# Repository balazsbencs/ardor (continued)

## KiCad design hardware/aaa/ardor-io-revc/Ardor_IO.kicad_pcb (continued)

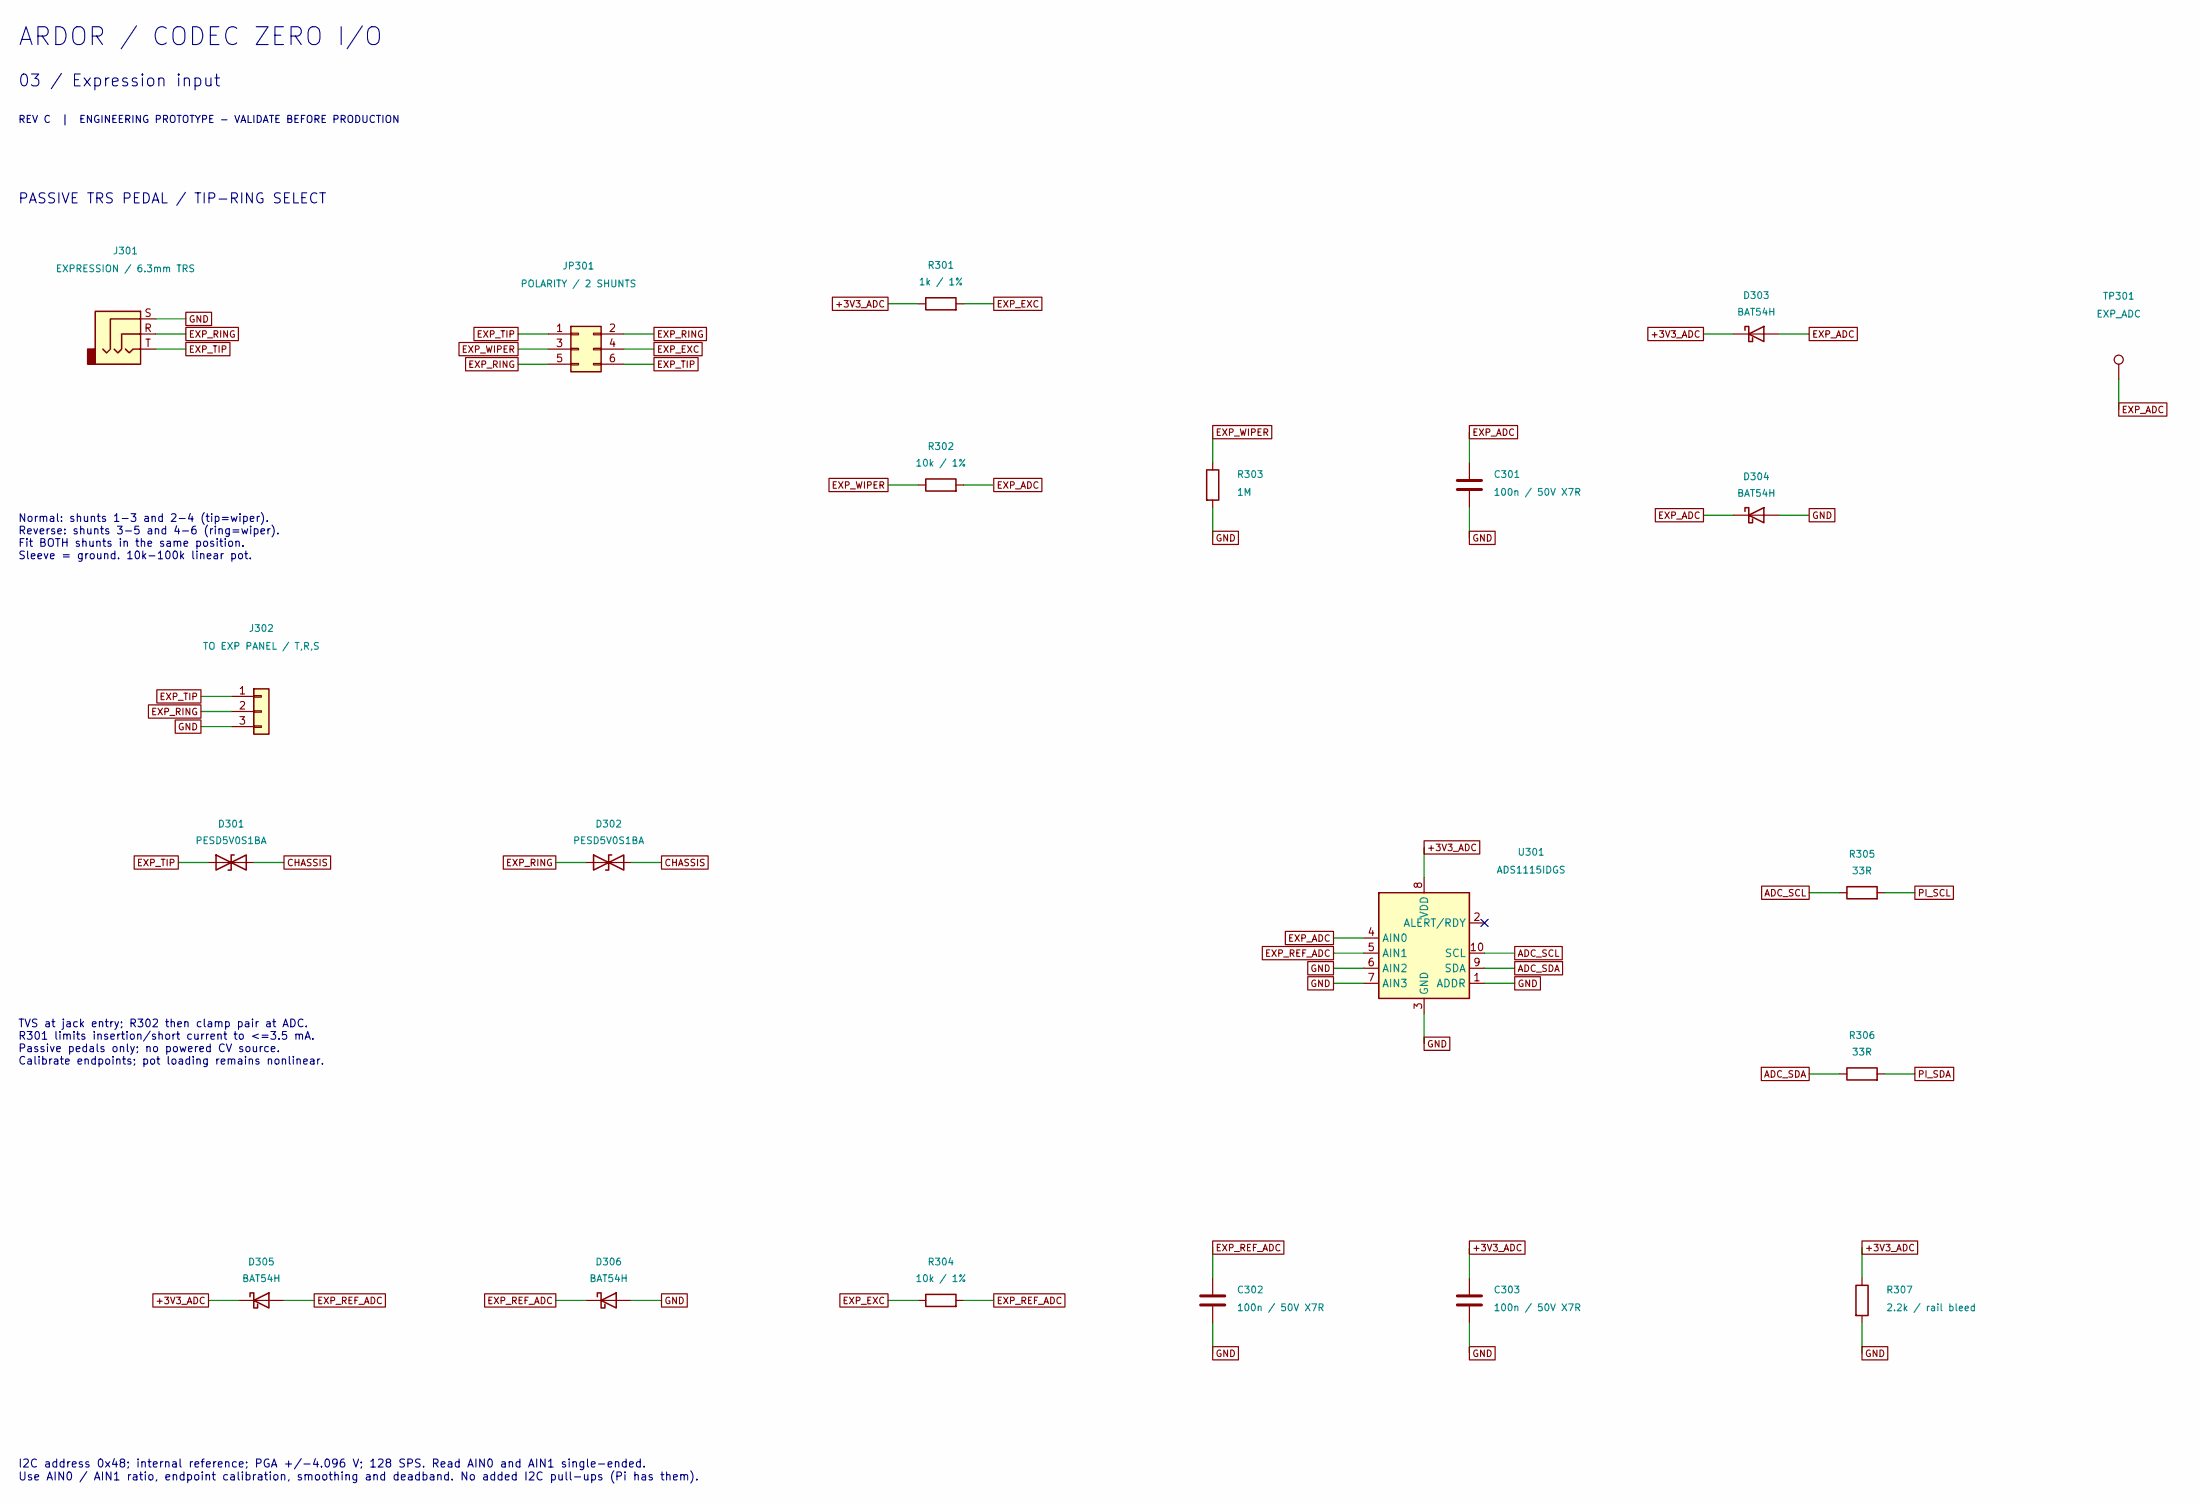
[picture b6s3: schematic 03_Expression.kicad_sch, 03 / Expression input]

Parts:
C301, C302, C303: 100n / 50V X7R; C_0603_1608Metric; MPN YAGEO CC0603KRX7R9BB104; JLCPCB Part # C14663
D301, D302: PESD5V0S1BA; D_SOD-323; MPN Nexperia PESD5V0S1BA,115; JLCPCB Part # C19224
D303, D304, D305, D306: BAT54H; D_SOD-123F; MPN Nexperia BAT54H,115; JLCPCB Part # C426769
J301: EXPRESSION / 6.3mm TRS
J302: TO EXP PANEL / T,R,S; PinHeader_1x03_P2.54mm_Vertical
JP301: POLARITY / 2 SHUNTS; PinHeader_2x03_P2.54mm_Vertical
R301: 1k / 1%; R_0603_1608Metric; MPN UNI-ROYAL 0603WAF1001T5E; JLCPCB Part # C21190
R302, R304: 10k / 1%; R_0603_1608Metric; MPN UNI-ROYAL 0603WAF1002T5E; JLCPCB Part # C25804
R303: 1M; R_0603_1608Metric; MPN UNI-ROYAL 0603WAF1004T5E; JLCPCB Part # C22935
R305, R306: 33R; R_0603_1608Metric; MPN UNI-ROYAL 0603WAF330JT5E; JLCPCB Part # C23140
R307: 2.2k / rail bleed; R_0603_1608Metric; MPN UNI-ROYAL 0603WAF2201T5E; JLCPCB Part # C4190
TP301: EXP_ADC; TestPoint_Pad_D1.5mm
U301: ADS1115IDGS; VSSOP-10_3x3mm_P0.5mm; MPN TI ADS1115IDGSR; JLCPCB Part # C37593

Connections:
+3V3_ADC: C303.1, D303.1 (K), D305.1 (K), R301.1, R307.1, U301.8 (VDD); also elsewhere on the board
ADC_SCL: R305.1, U301.10 (SCL)
ADC_SDA: R306.1, U301.9 (SDA)
CHASSIS: D301.2 (A2), D302.2 (A2); also elsewhere on the board
EXP_ADC: C301.1, D303.2 (A), D304.1 (K), R302.2, TP301.1, U301.4 (AIN0)
EXP_EXC: JP301.4, R301.2, R304.1
EXP_REF_ADC: C302.1, D305.2 (A), D306.1 (K), R304.2, U301.5 (AIN1)
EXP_RING: D302.1 (A1), J301.R, J302.2, JP301.2, JP301.5
EXP_TIP: D301.1 (A1), J301.T, J302.1, JP301.1, JP301.6
EXP_WIPER: JP301.3, R302.1, R303.1
GND: C301.2, C302.2, C303.2, D304.2 (A), D306.2 (A), J301.S, J302.3, R303.2, R307.2, U301.1 (ADDR), U301.3 (GND), U301.6 (AIN2), U301.7 (AIN3); also elsewhere on the board
PI_SCL: R305.2; also elsewhere on the board
PI_SDA: R306.2; also elsewhere on the board

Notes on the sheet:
ARDOR / CODEC ZERO I/O
03 / Expression input
REV C | ENGINEERING PROTOTYPE - VALIDATE BEFORE PRODUCTION
PASSIVE TRS PEDAL / TIP-RING SELECT
Normal: shunts 1-3 and 2-4 (tip=wiper). Reverse: shunts 3-5 and 4-6 (ring=wiper). Fit BOTH shunts in the same position. Sleeve = ground. 10k-100k linear pot.
TVS at jack entry; R302 then clamp pair at ADC. R301 limits insertion/short current to <=3.5 mA. Passive pedals only; no powered CV source. Calibrate endpoints; pot loading remains nonlinear.
I2C address 0x48; internal reference; PGA +/-4.096 V; 128 SPS. Read AIN0 and AIN1 single-ended. Use AIN0 / AIN1 ratio, endpoint calibration, smoothing and deadband. No added I2C pull-ups (Pi has them).

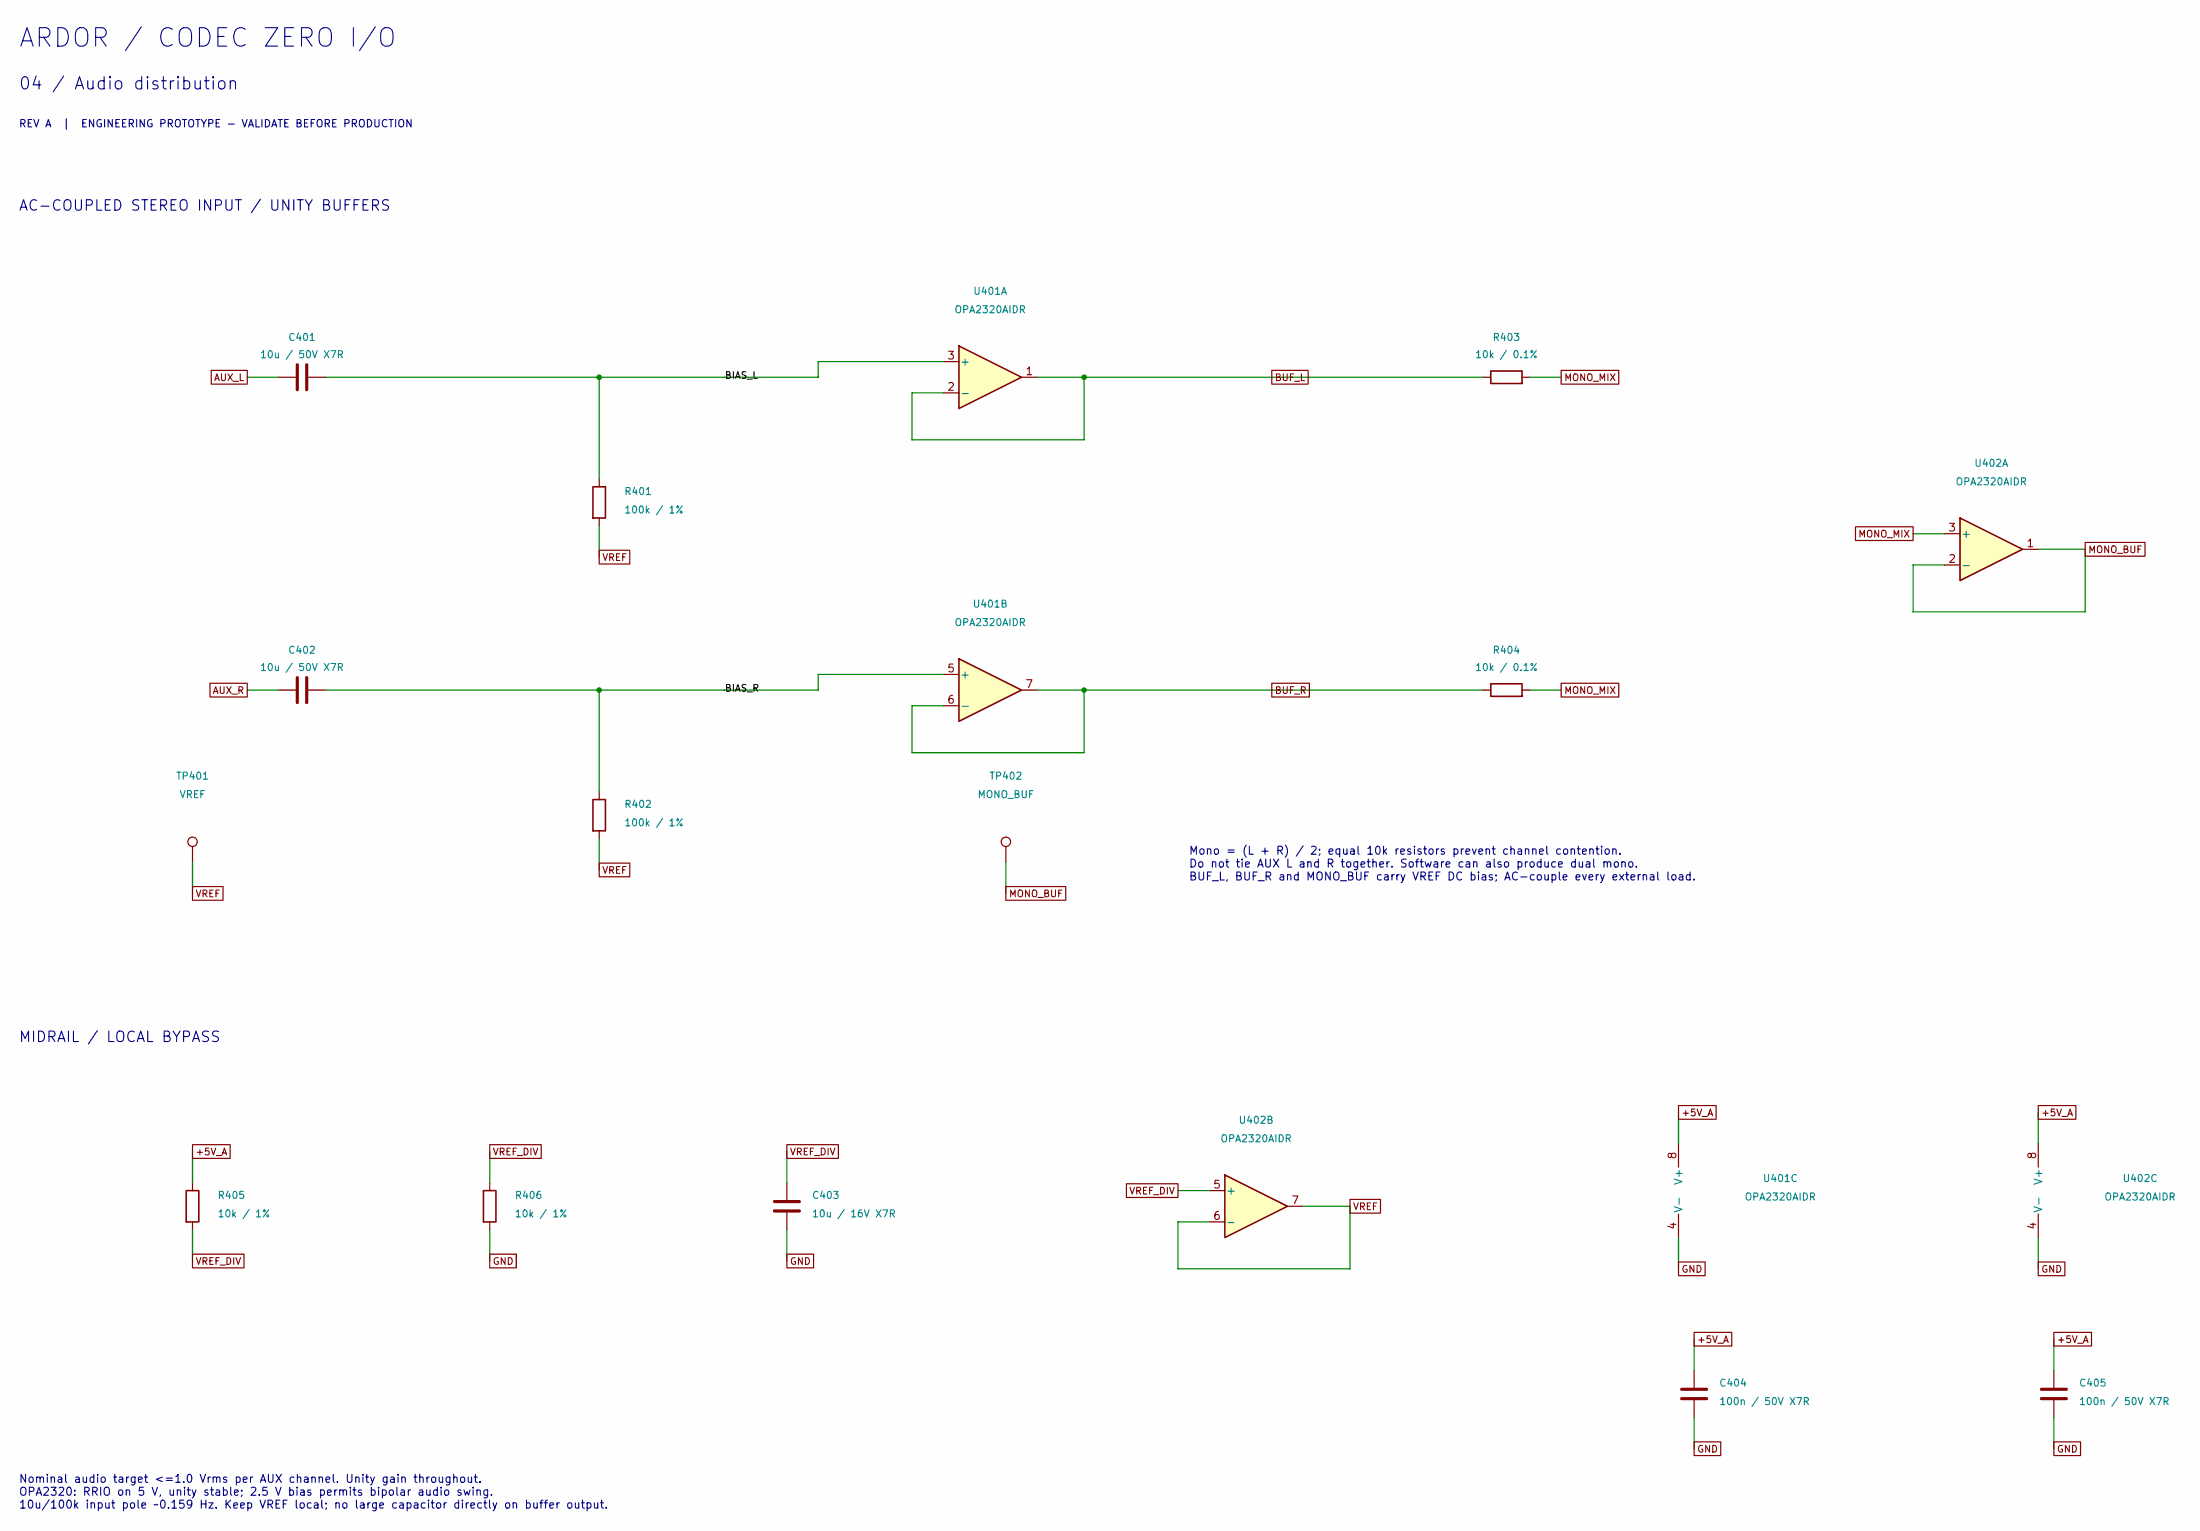
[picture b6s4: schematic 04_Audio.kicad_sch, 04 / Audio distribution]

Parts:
C401, C402: 10u / 50V X7R; C_1206_3216Metric; MPN Samsung CL31B106KBHNNNE; JLCPCB Part # C89632
C403: 10u / 16V X7R; C_0805_2012Metric; MPN Samsung CL21B106KOQNNNE; JLCPCB Part # C95841
C404, C405: 100n / 50V X7R; C_0603_1608Metric; MPN YAGEO CC0603KRX7R9BB104; JLCPCB Part # C14663
R401, R402: 100k / 1%; R_0603_1608Metric; MPN UNI-ROYAL 0603WAF1003T5E; JLCPCB Part # C25803
R403, R404: 10k / 0.1%; R_0603_1608Metric; MPN YAGEO RT0603BRD0710KL; JLCPCB Part # C95204
R405, R406: 10k / 1%; R_0603_1608Metric; MPN UNI-ROYAL 0603WAF1002T5E; JLCPCB Part # C25804
TP401: VREF; TestPoint_Pad_D1.5mm
TP402: MONO_BUF; TestPoint_Pad_D1.5mm
U401, U402: OPA2320AIDR; SOIC-8_3.9x4.9mm_P1.27mm; MPN TI OPA2320AIDR; JLCPCB Part # C2863402

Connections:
+5V_A: C404.1, C405.1, R405.1, U401.8 (V+), U402.8 (V+); also elsewhere on the board
/04 / Audio distribution/BIAS_L: C401.2, R401.1, U401.3 (+)
/04 / Audio distribution/BIAS_R: C402.2, R402.1, U401.5 (+)
/04 / Audio distribution/BUF_L: R403.1, U401.1, U401.2 (-)
/04 / Audio distribution/BUF_R: R404.1, U401.6 (-), U401.7
AUX_L: C401.1; also elsewhere on the board
AUX_R: C402.1; also elsewhere on the board
GND: C403.2, C404.2, C405.2, R406.2, U401.4 (V-), U402.4 (V-); also elsewhere on the board
MONO_MIX: R403.2, R404.2, U402.3 (+)
VREF: R401.2, R402.2, TP401.1, U402.6 (-), U402.7
VREF_DIV: C403.1, R405.2, R406.1, U402.5 (+)

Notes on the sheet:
ARDOR / CODEC ZERO I/O
04 / Audio distribution
REV A | ENGINEERING PROTOTYPE - VALIDATE BEFORE PRODUCTION
AC-COUPLED STEREO INPUT / UNITY BUFFERS
Mono = (L + R) / 2; equal 10k resistors prevent channel contention. Do not tie AUX L and R together. Software can also produce dual mono. BUF_L, BUF_R and MONO_BUF carry VREF DC bias; AC-couple every external load.
MIDRAIL / LOCAL BYPASS
Nominal audio target <=1.0 Vrms per AUX channel. Unity gain throughout. OPA2320: RRIO on 5 V, unity stable; 2.5 V bias permits bipolar audio swing. 10u/100k input pole ~0.159 Hz. Keep VREF local; no large capacitor directly on buffer output.

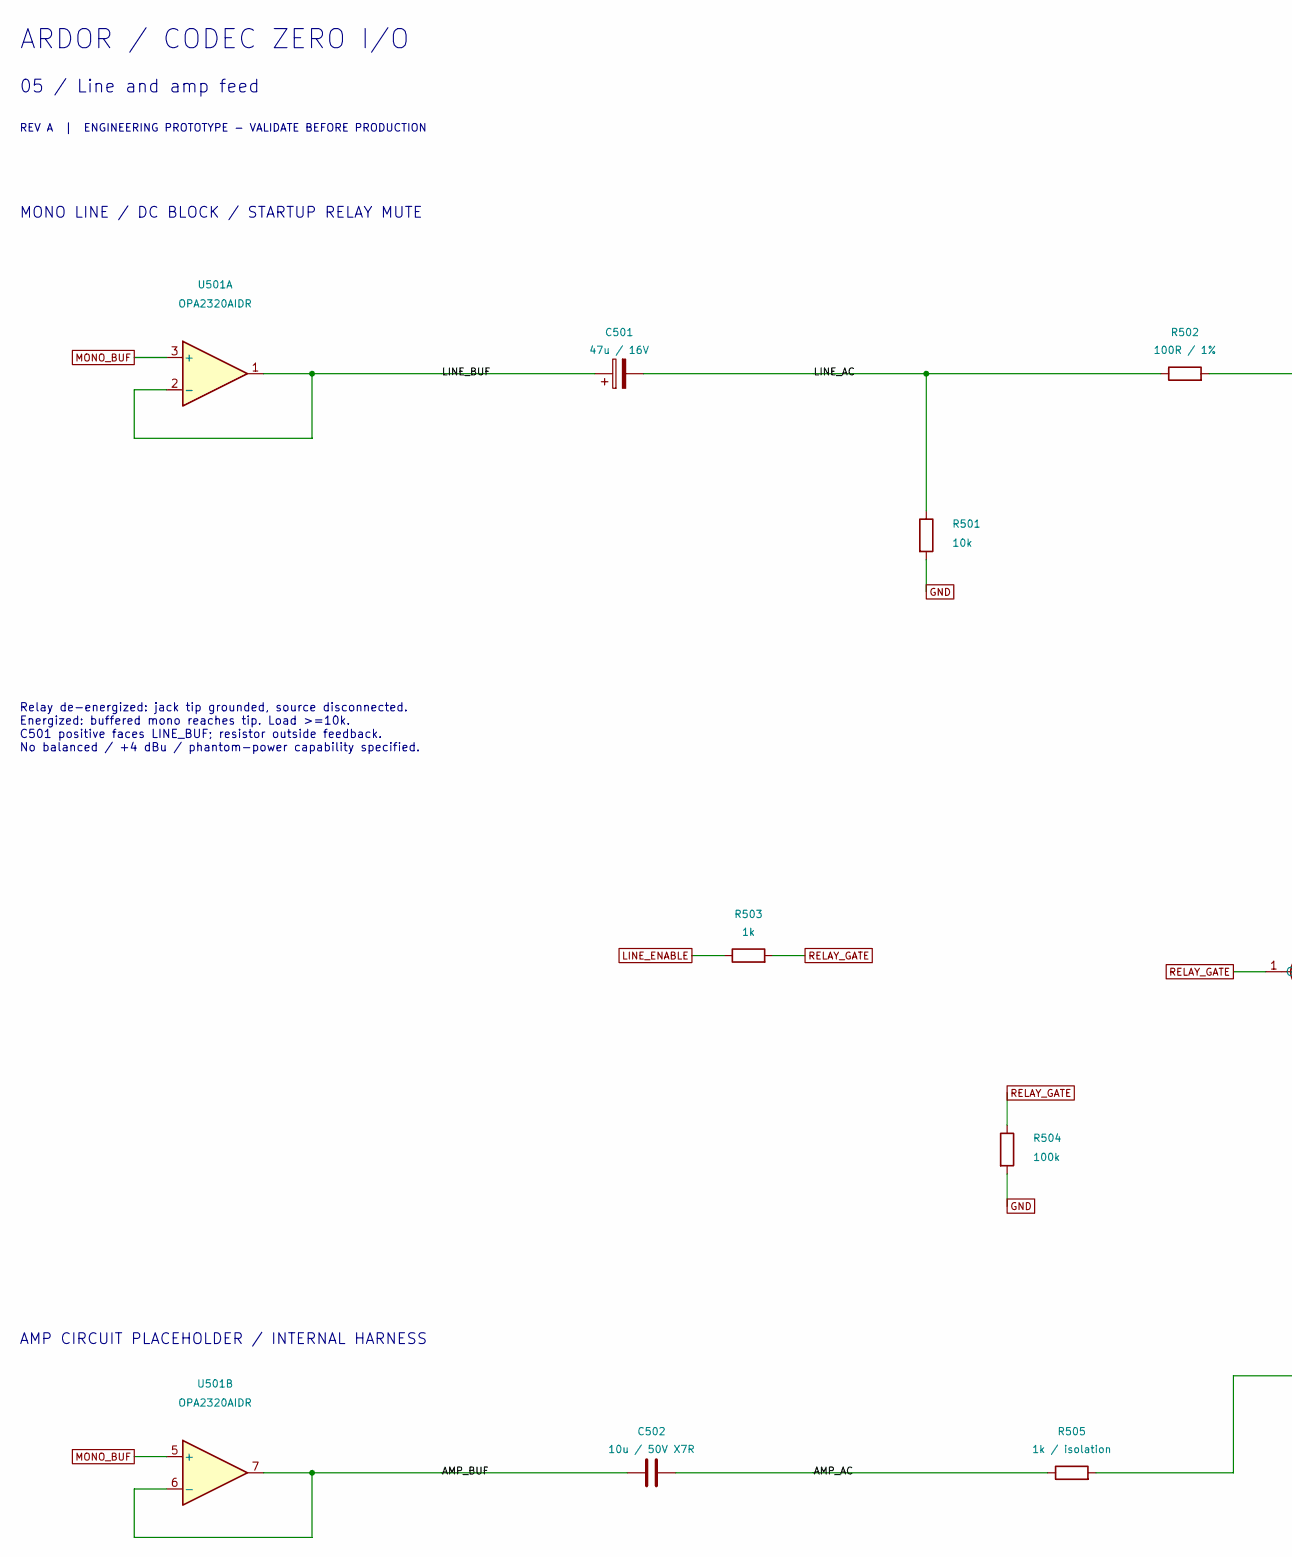
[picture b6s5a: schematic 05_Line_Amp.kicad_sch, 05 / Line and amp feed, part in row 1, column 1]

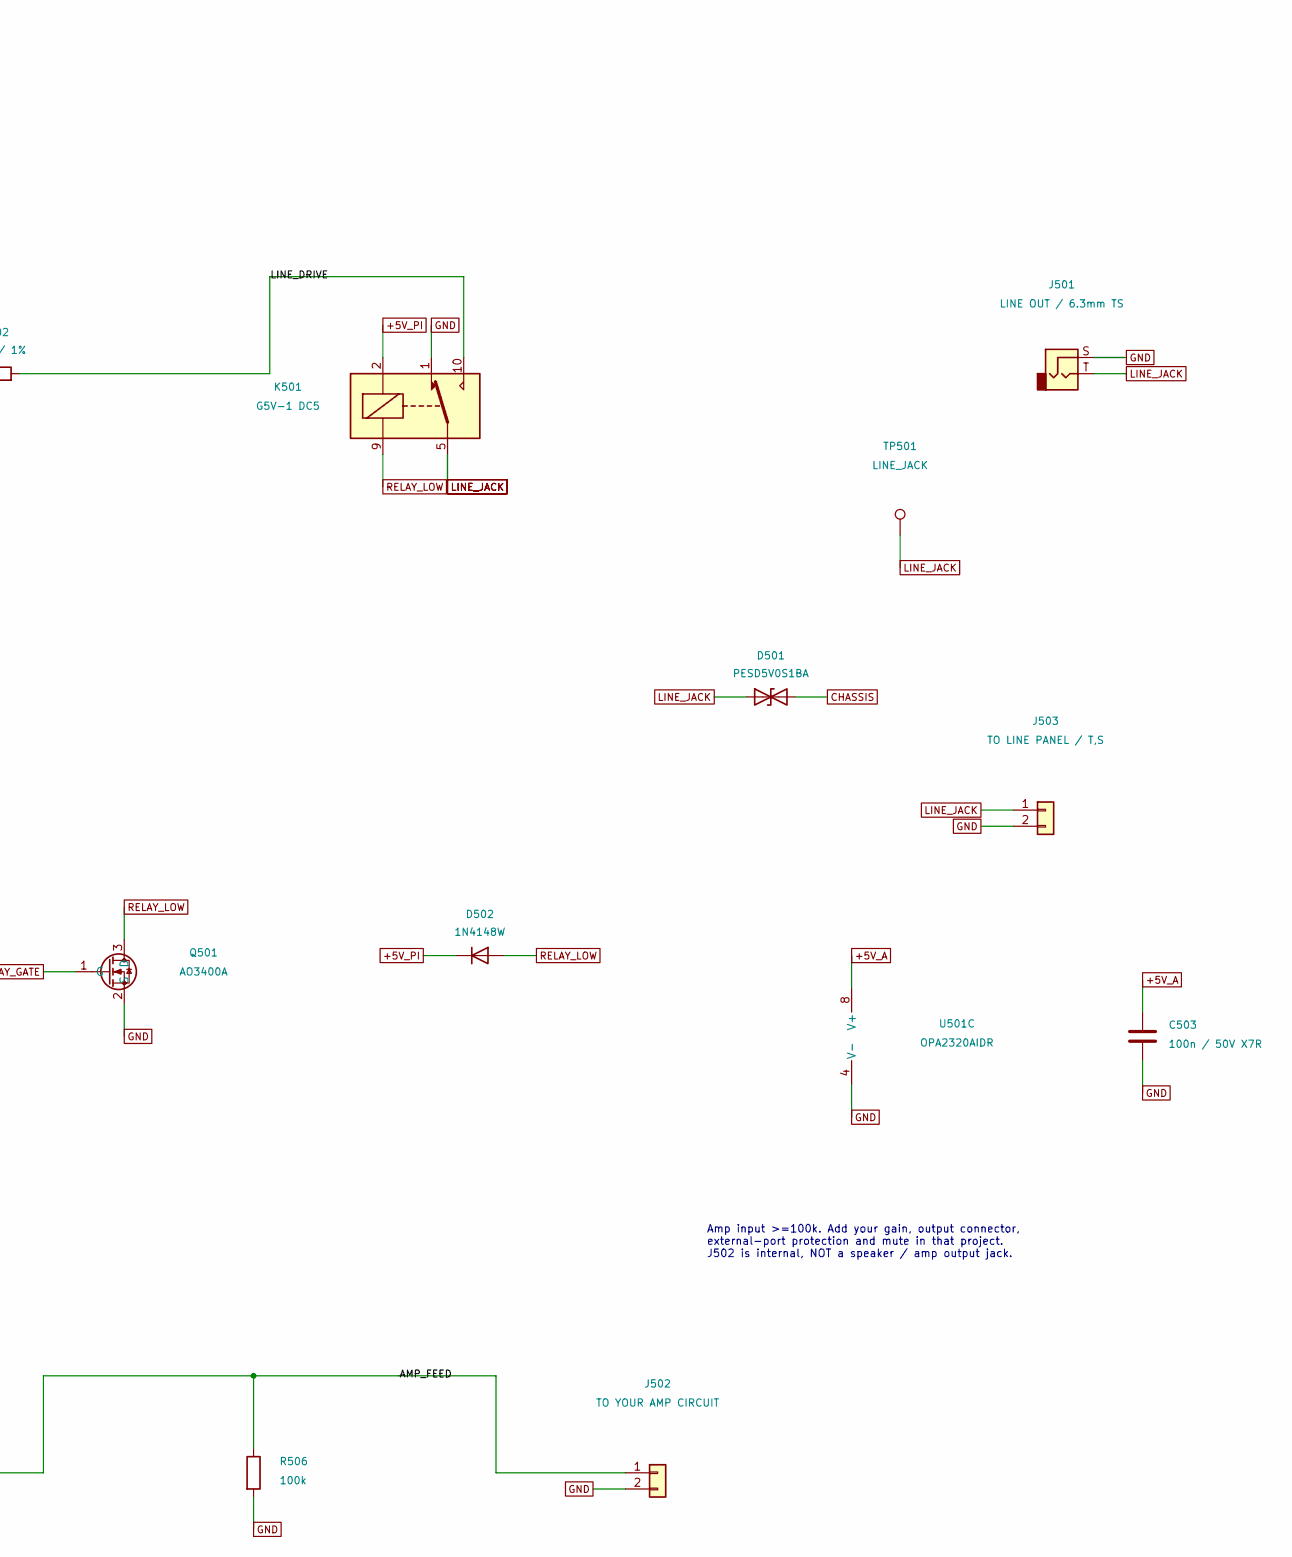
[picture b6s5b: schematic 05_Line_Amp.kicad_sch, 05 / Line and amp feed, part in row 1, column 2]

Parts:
C501: 47u / 16V; CP_Elec_Panasonic_FK_D6.3_H5.8; MPN Panasonic EEEFK1C470P; JLCPCB Part # C336261
C502: 10u / 50V X7R; C_1206_3216Metric; MPN Samsung CL31B106KBHNNNE; JLCPCB Part # C89632
C503: 100n / 50V X7R; C_0603_1608Metric; MPN YAGEO CC0603KRX7R9BB104; JLCPCB Part # C14663
D501: PESD5V0S1BA; D_SOD-323; MPN Nexperia PESD5V0S1BA,115; JLCPCB Part # C19224
D502: 1N4148W; D_SOD-123; MPN ST(Semtech) 1N4148W; JLCPCB Part # C81598
J501: LINE OUT / 6.3mm TS
J502: TO YOUR AMP CIRCUIT; PinHeader_1x02_P2.54mm_Vertical
J503: TO LINE PANEL / T,S; PinHeader_1x02_P2.54mm_Vertical
K501: G5V-1 DC5; Relay_SPDT_Omron_G5V-1; MPN Omron G5V-1 DC5
Q501: AO3400A; SOT-23; MPN Alpha & Omega AO3400A; JLCPCB Part # C20917
R501: 10k; R_0603_1608Metric; MPN UNI-ROYAL 0603WAF1002T5E; JLCPCB Part # C25804
R502: 100R / 1%; R_0603_1608Metric; MPN UNI-ROYAL 0603WAF1000T5E; JLCPCB Part # C22775
R503: 1k; R_0603_1608Metric; MPN UNI-ROYAL 0603WAF1001T5E; JLCPCB Part # C21190
R504, R506: 100k; R_0603_1608Metric; MPN UNI-ROYAL 0603WAF1003T5E; JLCPCB Part # C25803
R505: 1k / isolation; R_0603_1608Metric; MPN UNI-ROYAL 0603WAF1001T5E; JLCPCB Part # C21190
TP501: LINE_JACK; TestPoint_Pad_D1.5mm
U501: OPA2320AIDR; SOIC-8_3.9x4.9mm_P1.27mm; MPN TI OPA2320AIDR; JLCPCB Part # C2863402

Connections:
+5V_PI: D502.1 (K), K501.2; also elsewhere on the board
/05 / Line and amp feed/AMP_AC: C502.2, R505.1
/05 / Line and amp feed/AMP_FEED: J502.1, R505.2, R506.1
/05 / Line and amp feed/LINE_AC: C501.2, R501.1, R502.1
/05 / Line and amp feed/LINE_DRIVE: K501.10, R502.2
CHASSIS: D501.2 (A2); also elsewhere on the board
GND: C503.2, J501.S, J502.2, J503.2, K501.1, Q501.2 (S), R501.2, R504.2, R506.2, U501.4 (V-); also elsewhere on the board
LINE_ENABLE: R503.1; also elsewhere on the board
LINE_JACK: D501.1 (A1), J501.T, J503.1, K501.5, K501.6, TP501.1
unnamed: C503.1, U501.8 (V+)
unnamed: U501.3 (+), U501.5 (+)
RELAY_GATE: Q501.1 (G), R503.2, R504.1
RELAY_LOW: D502.2 (A), K501.9, Q501.3 (D)

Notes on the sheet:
ARDOR / CODEC ZERO I/O
05 / Line and amp feed
REV A | ENGINEERING PROTOTYPE - VALIDATE BEFORE PRODUCTION
MONO LINE / DC BLOCK / STARTUP RELAY MUTE
Relay de-energized: jack tip grounded, source disconnected. Energized: buffered mono reaches tip. Load >=10k. C501 positive faces LINE_BUF; resistor outside feedback. No balanced / +4 dBu / phantom-power capability specified.
AMP CIRCUIT PLACEHOLDER / INTERNAL HARNESS
Amp input >=100k. Add your gain, output connector, external-port protection and mute in that project. J502 is internal, NOT a speaker / amp output jack.

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
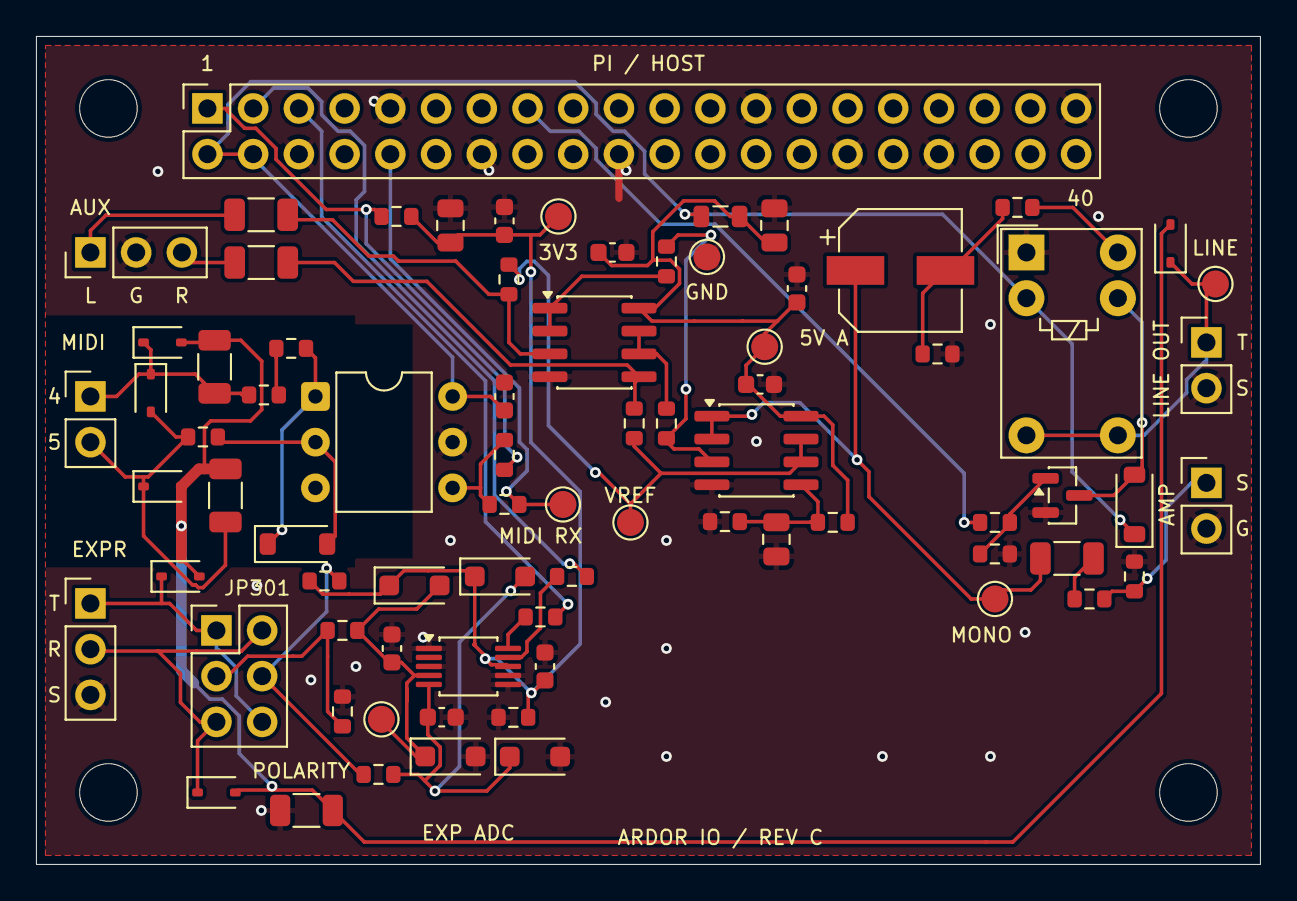
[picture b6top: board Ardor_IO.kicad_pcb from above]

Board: 2 copper layers, 68.0 x 46.0 mm, 81 parts (0 on the bottom side), 41 nets.

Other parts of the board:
H1, H2, H3, H4: M3 / PROVISIONAL; MountingHole_3.2mm_M3

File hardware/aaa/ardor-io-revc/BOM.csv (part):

Reference,Value,MPN,Footprint,Datasheet,Assembly,Sheet,JLCPCB Part #
J101,PI 40-PIN HEADER,Samtec SSQ-120-03-G-D (verify stack height),Connector_PinSocket_2.54mm:PinSocket_2x20_P2.54mm_Vertical,,PCB,1,
J102,CODEC AUX L / GND / R,,Connector_PinHeader_2.54mm:PinHeader_1x03_P2.54mm_Vertical,,PCB,1,
FB101,600R @100MHz,Murata BLM21PG601SN1D,Inductor_SMD:L_0805_2012Metric,https://www.murata.com/products/productdata/8796738977822/EN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,PCB,1,C41556732
C101,22u / 25V X5R,Samsung Electro-Mechanics CL21A226MAQNNNE,Capacitor_SMD:C_0805_2012Metric,https://www.lcsc.com/datasheet/lcsc_datasheet_2304140030_Sam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,PCB,1,C45783
C102,100n / 50V X7R,YAGEO CC0603KRX7R9BB104,Capacitor_SMD:C_0603_1608Metric,https://www.lcsc.com/datasheet/lcsc_datasheet_2211101700_YAG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,PCB,1,C14663
FB102,120R @100MHz,Murata Electronics BLM18PG121SN1D,Resistor_SMD:R_0603_1608Metric,https://www.lcsc.com/datasheet/lcsc_datasheet_2304140030_Mur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,PCB,1,C14709
C103,10u / 25V X5R,Samsung Electro-Mechanics CL21A106KAYNNNE,Capacitor_SMD:C_0805_2012Metric,https://www.lcsc.com/datasheet/lcsc_datasheet_2304140030_Sam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,PCB,1,C15850
C104,100n / 50V X7R,YAGEO CC0603KRX7R9BB104,Capacitor_SMD:C_0603_1608Metric,https://www.lcsc.com/datasheet/lcsc_datasheet_2211101700_YAG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,PCB,1,C14663
R101,0R / chassis bond,UNI-ROYAL 1206W4F0000T5E,Resistor_SMD:R_1206_3216Metric,https://www.lcsc.com/datasheet/lcsc_datasheet_2206010200_UNI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,PCB,1,C17888
J201,MIDI IN - PANEL DIN,,,,Panel / wired,2,
FB201,120R @100MHz,Murata Electronics BLM18PG121SN1D,Resistor_SMD:R_0603_1608Metric,https://www.lcsc.com/datasheet/lcsc_datasheet_2304140030_Mur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,PCB,2,C14709
R201,220R / 1%,UNI-ROYAL 0603WAF2200T5E,Resistor_SMD:R_0603_1608Metric,https://www.lcsc.com/datasheet/lcsc_datasheet_2206010130_UNI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,PCB,2,C22962
FB202,120R @100MHz,Murata Electronics BLM18PG121SN1D,Resistor_SMD:R_0603_1608Metric,https://www.lcsc.com/datasheet/lcsc_datasheet_2304140030_Mur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,PCB,2,C14709
D201,1N4148W,ST(Semtech) 1N4148W,Diode_SMD:D_SOD-123,https://www.lcsc.com/datasheet/lcsc_datasheet_1811061725_ST-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,PCB,2,C81598
U201,H11L1M,onsemi H11L1M,Package_DIP:DIP-6_W7.62mm,https://www.onsemi.com/pdf/datasheet/h11l3m-d.pdf,PCB,2,
C201,100n / 50V X7R,YAGEO CC0603KRX7R9BB104,Capacitor_SMD:C_0603_1608Metric,https://www.lcsc.com/datasheet/lcsc_datasheet_2211101700_YAG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,PCB,2,C14663
R202,1k / 1%,UNI-ROYAL 0603WAF1001T5E,Resistor_SMD:R_0603_1608Metric,https://www.lcsc.com/datasheet/lcsc_datasheet_2206010130_UNI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,PCB,2,C21190
R203,100R,UNI-ROYAL 0603WAF1000T5E,Resistor_SMD:R_0603_1608Metric,https://www.lcsc.com/datasheet/lcsc_datasheet_2411221126_UNI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,PCB,2,C22775
D202,PESD5V0S1BA,"Nexperia PESD5V0S1BA,115",Diode_SMD:D_SOD-323,https://assets.nexperia.com/documents/data-sheet/PESD5V0S1BA.pdf,PCB,2,C19224
C202,100p / 1kV C0G,CCTC TCC1206COG101J102DT,Capacitor_SMD:C_1206_3216Metric,https://wmsc.lcsc.com/wmsc/upload/file/pdf/v2/lcsc/230414003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,PCB,2,C367316
C203,100p / 1kV C0G,CCTC TCC1206COG101J102DT,Capacitor_SMD:C_1206_3216Metric,https://wmsc.lcsc.com/wmsc/upload/file/pdf/v2/lcsc/230414003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,PCB,2,C367316
D203,PESD24VL1BA,"Nexperia PESD24VL1BA,115",Diode_SMD:D_SOD-323,https://assets.nexperia.com/documents/data-sheet/PESD24VL1BA.pdf,PCB,2,C69324
D204,PESD24VL1BA,"Nexperia PESD24VL1BA,115",Diode_SMD:D_SOD-323,https://assets.nexperia.com/documents/data-sheet/PESD24VL1BA.pdf,PCB,2,C69324
J301,EXPRESSION / 6.3mm TRS,,,,Panel / wired,3,
JP301,POLARITY / 2 SHUNTS,,Connector_PinHeader_2.54mm:PinHeader_2x03_P2.54mm_Vertical,,PCB,3,
R301,1k / 1%,UNI-ROYAL 0603WAF1001T5E,Resistor_SMD:R_0603_1608Metric,https://www.lcsc.com/datasheet/lcsc_datasheet_2206010130_UNI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,PCB,3,C21190
R302,10k / 1%,UNI-ROYAL 0603WAF1002T5E,Resistor_SMD:R_0603_1608Metric,https://www.lcsc.com/datasheet/lcsc_datasheet_2206010045_UNI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,PCB,3,C25804
R303,1M,UNI-ROYAL 0603WAF1004T5E,Resistor_SMD:R_0603_1608Metric,https://www.lcsc.com/datasheet/lcsc_datasheet_2206010130_UNI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,PCB,3,C22935
C301,100n / 50V X7R,YAGEO CC0603KRX7R9BB104,Capacitor_SMD:C_0603_1608Metric,https://www.lcsc.com/datasheet/lcsc_datasheet_2211101700_YAG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,PCB,3,C14663
D303,BAT54H,"Nexperia BAT54H,115",Diode_SMD:D_SOD-123F,https://www.lcsc.com/datasheet/lcsc_datasheet_2407241029_Nex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,PCB,3,C426769
D304,BAT54H,"Nexperia BAT54H,115",Diode_SMD:D_SOD-123F,https://www.lcsc.com/datasheet/lcsc_datasheet_2407241029_Nex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,PCB,3,C426769
D301,PESD5V0S1BA,"Nexperia PESD5V0S1BA,115",Diode_SMD:D_SOD-323,https://assets.nexperia.com/documents/data-sheet/PESD5V0S1BA.pdf,PCB,3,C19224
D302,PESD5V0S1BA,"Nexperia PESD5V0S1BA,115",Diode_SMD:D_SOD-323,https://assets.nexperia.com/documents/data-sheet/PESD5V0S1BA.pdf,PCB,3,C19224
U301,ADS1115IDGS,TI ADS1115IDGSR,Package_SO:VSSOP-10_3x3mm_P0.5mm,https://www.ti.com/lit/ds/symlink/ads1115.pdf,PCB,3,C37593
R304,10k / 1%,UNI-ROYAL 0603WAF1002T5E,Resistor_SMD:R_0603_1608Metric,https://www.lcsc.com/datasheet/lcsc_datasheet_2206010045_UNI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,PCB,3,C25804
C302,100n / 50V X7R,YAGEO CC0603KRX7R9BB104,Capacitor_SMD:C_0603_1608Metric,https://www.lcsc.com/datasheet/lcsc_datasheet_2211101700_YAG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,PCB,3,C14663
C303,100n / 50V X7R,YAGEO CC0603KRX7R9BB104,Capacitor_SMD:C_0603_1608Metric,https://www.lcsc.com/datasheet/lcsc_datasheet_2211101700_YAG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,PCB,3,C14663
R305,33R,UNI-ROYAL 0603WAF330JT5E,Resistor_SMD:R_0603_1608Metric,https://www.lcsc.com/datasheet/lcsc_datasheet_2206010116_UNI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,PCB,3,C23140
R306,33R,UNI-ROYAL 0603WAF330JT5E,Resistor_SMD:R_0603_1608Metric,https://www.lcsc.com/datasheet/lcsc_datasheet_2206010116_UNI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,PCB,3,C23140
R307,2.2k / rail bleed,UNI-ROYAL 0603WAF2201T5E,Resistor_SMD:R_0603_1608Metric,https://www.lcsc.com/datasheet/lcsc_datasheet_2206010230_UNI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,PCB,3,C4190
D305,BAT54H,"Nexperia BAT54H,115",Diode_SMD:D_SOD-123F,https://www.lcsc.com/datasheet/lcsc_datasheet_2407241029_Nex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,PCB,3,C426769
D306,BAT54H,"Nexperia BAT54H,115",Diode_SMD:D_SOD-123F,https://www.lcsc.com/datasheet/lcsc_datasheet_2407241029_Nex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,PCB,3,C426769
C401,10u / 50V X5R,Samsung Electro-Mechanics CL31A106KBHNNNE,Capacitor_SMD:C_1206_3216Metric,https://www.lcsc.com/datasheet/lcsc_datasheet_2304140030_Sam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,PCB,4,C13585
R401,100k / 1%,UNI-ROYAL 0603WAF1003T5E,Resistor_SMD:R_0603_1608Metric,https://www.lcsc.com/datasheet/lcsc_datasheet_2206010045_UNI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,PCB,4,C25803
U401,TLV9002IDR,Texas Instruments TLV9002IDR,Package_SO:SOIC-8_3.9x4.9mm_P1.27mm,https://www.lcsc.com/datasheet/lcsc_datasheet_2304140030_Tex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,PCB,4,C398360
R403,10k / 1%,UNI-ROYAL 0603WAF1002T5E,Resistor_SMD:R_0603_1608Metric,https://www.lcsc.com/datasheet/lcsc_datasheet_2206010045_UNI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,PCB,4,C25804
C402,10u / 50V X5R,Samsung Electro-Mechanics CL31A106KBHNNNE,Capacitor_SMD:C_1206_3216Metric,https://www.lcsc.com/datasheet/lcsc_datasheet_2304140030_Sam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,PCB,4,C13585
R402,100k / 1%,UNI-ROYAL 0603WAF1003T5E,Resistor_SMD:R_0603_1608Metric,https://www.lcsc.com/datasheet/lcsc_datasheet_2206010045_UNI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,PCB,4,C25803
R404,10k / 1%,UNI-ROYAL 0603WAF1002T5E,Resistor_SMD:R_0603_1608Metric,https://www.lcsc.com/datasheet/lcsc_datasheet_2206010045_UNI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,PCB,4,C25804
U402,TLV9002IDR,Texas Instruments TLV9002IDR,Package_SO:SOIC-8_3.9x4.9mm_P1.27mm,https://www.lcsc.com/datasheet/lcsc_datasheet_2304140030_Tex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,PCB,4,C398360
R405,10k / 1%,UNI-ROYAL 0603WAF1002T5E,Resistor_SMD:R_0603_1608Metric,https://www.lcsc.com/datasheet/lcsc_datasheet_2206010045_UNI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,PCB,4,C25804
R406,10k / 1%,UNI-ROYAL 0603WAF1002T5E,Resistor_SMD:R_0603_1608Metric,https://www.lcsc.com/datasheet/lcsc_datasheet_2206010045_UNI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,PCB,4,C25804
C403,10u / 25V X5R,Samsung Electro-Mechanics CL21A106KAYNNNE,Capacitor_SMD:C_0805_2012Metric,https://www.lcsc.com/datasheet/lcsc_datasheet_2304140030_Sam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,PCB,4,C15850
C404,100n / 50V X7R,YAGEO CC0603KRX7R9BB104,Capacitor_SMD:C_0603_1608Metric,https://www.lcsc.com/datasheet/lcsc_datasheet_2211101700_YAG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,PCB,4,C14663
C405,100n / 50V X7R,YAGEO CC0603KRX7R9BB104,Capacitor_SMD:C_0603_1608Metric,https://www.lcsc.com/datasheet/lcsc_datasheet_2211101700_YAG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,PCB,4,C14663
C501,47u / 16V,Panasonic EEEFK1C470P,Ardor_Capacitor:CP_Elec_Panasonic_FK_D6.3_H5.8,https://industrial.panasonic.com/cdbs/www-data/pdf/RDE0000/A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,PCB,5,C336261
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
